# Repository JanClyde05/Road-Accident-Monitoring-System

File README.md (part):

# Road Accident Monitoring System (RAMS)

**Real-Time Highway Incident Detection, LoRa Long-Range Telemetry, Dual-Tier Edge AI, and Rescuer Command Center**

RAMS is an end-to-end, multi-tier emergency response platform engineered for real-time traffic accident detection and immediate rescue dispatch. Designed specifically for highway environments and rural road segments vulnerable to cellular coverage dropouts, RAMS pairs a custom wearable sensor relay node with high-rate inertial shock sensing, off-grid 433MHz LoRa long-range radio broadcast, dual-tier on-device neural edge classification, rider mobile telemetry synchronization, conversational voice AI, and a standalone command-center desktop application.

---

## 1. System Architecture & Information Pipeline

```
  +-------------------------------------------------------------------------------+
  |                             RIDER TIER (MOBILE)                               |
  |  Android Companion App (Kotlin / Jetpack Compose / Edge AI Engine)            |
  |  - 50Hz Continuous Inertial Sensing (Fused Accel/Gyro + Euler Horizon)        |
  |  - Dual-Tier Edge AI: 1D-CNN Kinematic Feature Extractor + SLM Reasoner       |
  |  - 100% Offline On-Device Voice AI Assistant & Wake-Word Canceler ("Hey RAMS")|
  |  - Background System Overlay: Pop-up AI assistant over Facebook / other apps  |
  |  - Dual-Band GNSS Coordinate Acquisition & Offline Hotspot Hazard Density     |
  |  - Medical & Identity Profile Management (Base62 Token, Photo CDN)            |
  |  - Cellular Fallback: Automated SMS Emergency Dispatch & Cloud REST Relay     |
  +---------------------------------------+---------------------------------------+
                                          |
                              BLE GATT (0xFFE0 / 0xFFE1)
                                          |
                                          v
  +-------------------------------------------------------------------------------+
  |                            WEARABLE RELAY TIER                                |
  |  RAMS Custom Wearable PCB (ESP32-S3FH4R2, Rev C EPDC Edition)                 |
  |  - 2-Stage Finite State Machine (Freefall -> Impact Spike -> Rest -> Latch)   |
  |  - On-Board MPU-6050 Motion Engine & Crash Logic (100Hz I2C)                  |
  |  - 30-Second Auditory / Visual Warning & False-Alarm Cancellation Button      |
  |  - WS2812B RGB Status Indication (Armed, SOS Alert, Low Battery)              |
  |  - On-Board Battery Management (TP4054 Charger + DW01A/FS8205A Protection)   |
  +---------------------------------------+---------------------------------------+
                                          |
                        433MHz LoRa Link (SX1278, SF9, CR 4/5)
                                          |
                                          v
  +-------------------------------------------------------------------------------+
  |                         BASE STATION RECEIVER TIER                            |
  |  LoRa Ground Station (ESP32-S3 Base Unit)                                     |
  |  - Continuous 433MHz Carrier Monitoring (SX1278 SPI Interface)               |
  |  - Dual-Stream Output: High-Speed USB Serial & Local Wi-Fi TCP/HTTP Bridge    |
  |  - LittleFS Offline Flash Store-and-Forward Emergency Queue                   |
  +-------------------+---------------------------------------+-------------------+
                      |                                       |
              USB Serial (115200)                      Wi-Fi / LAN TCP (8888)
                      |                                       |
                      +-------------------+-------------------+
                                          v
  +-------------------------------------------------------------------------------+
  |                        COMMAND CENTER & DISPATCH TIER                         |
  |  Windows Rescuer Desktop Application (C# .NET + React 19 / Leaflet Radar)     |
  |  - Zero-Configuration COM Port Auto-Detection & USB Ingestion Engine          |
  |  - Real-Time Incident Triage, Audible Klaxon Alerts, & Priority Queuing       |
  |  - Interactive Tactical Radar Map with Live Marker Tracking & ETA Calculation |
  |  - Spatial Machine Learning Hotspot Predictor & Incident Heatmap              |
  |  - Local JSON Data Persistence (incidents.json, registrations.json)           |
  |  - Netlify Cloud Backend Integration & Public Web Map Mirror                  |
  +-------------------------------------------------------------------------------+
```

---

## 2. Master Navigation Index: Focus Folders & Core Entry Points

This directory routing table allows human engineers and AI agents to locate and navigate every functional subsystem directly:

| Subsystem Domain | Primary Focus Folder | Key Entry Points & Core Files | Role & Capabilities |
|---|---|---|---|
| **Android Mobile App** | [`apps/android_app/`](file:///d:/Antigravity/Projects/Danger%20Monitoring%20System%20V2/apps/android_app/) | [`MainActivity.kt`](file:///d:/Antigravity/Projects/Danger%20Monitoring%20System%20V2/apps/android_app/app/src/main/java/com/example/MainActivity.kt)<br>[`RamsViewModel.kt`](file:///d:/Antigravity/Projects/Danger%20Monitoring%20System%20V2/apps/android_app/app/src/main/java/com/example/viewmodel/RamsViewModel.kt)<br>[`AndroidManifest.xml`](file:///d:/Antigravity/Projects/Danger%20Monitoring%20System%20V2/apps/android_app/app/src/main/AndroidManifest.xml) | Production Android Kotlin / Jetpack Compose application. Houses BLE GATT, GPS, real-time telemetry, and foreground service. |
| **Edge AI & Assistant** | [`apps/android_app/.../ai/`](file:///d:/Antigravity/Projects/Danger%20Monitoring%20System%20V2/apps/android_app/app/src/main/java/com/example/ai/) | [`SensorAiInferenceEngine.kt`](file:///d:/Antigravity/Projects/Danger%20Monitoring%20System%20V2/apps/android_app/app/src/main/java/com/example/ai/SensorAiInferenceEngine.kt)<br>[`VoiceAlarmCanceler.kt`](file:///d:/Antigravity/Projects/Danger%20Monitoring%20System%20V2/apps/android_app/app/src/main/java/com/example/ai/VoiceAlarmCanceler.kt)<br>[`RamsAiAssistantEngine.kt`](file:///d:/Antigravity/Projects/Danger%20Monitoring%20System%20V2/apps/android_app/app/src/main/java/com/example/ai/RamsAiAssistantEngine.kt) | Dual-tier edge neural model, 100% offline "Hey RAMS" wake-word recognizer, and personalized conversational companion. |
| **Standalone AI Suite** | [`apps/new_ai_applications/`](file:///d:/Antigravity/Projects/Danger%20Monitoring%20System%20V2/apps/new_ai_applications/) | [`mobile_ai_app/`](file:///d:/Antigravity/Projects/Danger%20Monitoring%20System%20V2/apps/new_ai_applications/mobile_ai_app/)<br>[`ai_resources_and_models/`](file:///d:/Antigravity/Projects/Danger%20Monitoring%20System%20V2/apps/new_ai_applications/ai_resources_and_models/)<br>[`FREE_MOTION_DATASETS_DIRECTORY.md`](file:///d:/Antigravity/Projects/Danger%20Monitoring%20System%20V2/apps/new_ai_applications/ai_resources_and_models/FREE_MOTION_DATASETS_DIRECTORY.md) | Synchronized standalone twin applications, motion benchmark datasets, and 1-click build pipelines. |
| **Wearable Firmware** | [`firmware/wearable_withApp/`](file:///d:/Antigravity/Projects/Danger%20Monitoring%20System%20V2/firmware/wearable_withApp/) | [`wearable_withApp.ino`](file:///d:/Antigravity/Projects/Danger%20Monitoring%20System%20V2/firmware/wearable_withApp/wearable_withApp.ino) | ESP32-S3 firmware with MPU-6050 100Hz FSM, ATGM336H GPS parsing, SX1278 LoRa uplink, BLE GATT server, and WS2812B NeoPixel. |
| **Base Station Firmware** | [`firmware/receiver_withDesktop/`](file:///d:/Antigravity/Projects/Danger%20Monitoring%20System%20V2/firmware/receiver_withDesktop/) | [`receiver_withDesktop.ino`](file:///d:/Antigravity/Projects/Danger%20Monitoring%20System%20V2/firmware/receiver_withDesktop/receiver_withDesktop.ino) | ESP32-S3 base station listening on 433MHz LoRa. Forwards alerts over USB Serial (`RAMS_PKT:...`) and Wi-Fi TCP/HTTP. |
| **Shared RF Protocol** | [`firmware/shared/`](file:///d:/Antigravity/Projects/Danger%20Monitoring%20System%20V2/firmware/shared/) | [`protocol.h`](file:///d:/Antigravity/Projects/Danger%20Monitoring%20System%20V2/firmware/shared/protocol.h) | Canonical C header defining packed binary RF structs (`LoRaAlertPacket`, `TelemetryPacket`), bitmasks, and RF channels. |
| **Command Center Desktop** | [`apps/desktop_app/`](file:///d:/Antigravity/Projects/Danger%20Monitoring%20System%20V2/apps/desktop_app/) | [`RescuerForm.cs`](file:///d:/Antigravity/Projects/Danger%20Monitoring%20System%20V2/apps/desktop_app/RescuerForm.cs)<br>[`HotspotPredictor.cs`](file:///d:/Antigravity/Projects/Danger%20Monitoring%20System%20V2/apps/desktop_app/HotspotPredictor.cs)<br>[`www/index.html`](file:///d:/Antigravity/Projects/Danger%20Monitoring%20System%20V2/apps/desktop_app/www/index.html) | Windows Rescuer Operations app (C# .NET / WebView2 + React 19). Handles serial auto-detect, klaxon alerts, and incident triage. |
| **Cloud Web Mirror** | [`apps/backend/`](file:///d:/Antigravity/Projects/Danger%20Monitoring%20System%20V2/apps/backend/) | [`src/App.tsx`](file:///d:/Antigravity/Projects/Danger%20Monitoring%20System%20V2/apps/backend/src/App.tsx)<br>[`netlify.toml`](file:///d:/Antigravity/Projects/Danger%20Monitoring%20System%20V2/apps/backend/netlify.toml) | React 19 / Leaflet live dispatch map hosted on Netlify Serverless for supervisor and field hospital visibility. |
| **Hardware & PCB CAD** | [`hardware/KiCAD Files/Antigravity Build/RAMS - PCB - Rev C/`](file:///d:/Antigravity/Projects/Danger%20Monitoring%20System%20V2/hardware/KiCAD%20Files/Antigravity%20Build/RAMS%20-%20PCB%20-%20Rev%20C/) | [`RAMS - PCB.kicad_sch`](file:///d:/Antigravity/Projects/Danger%20Monitoring%20System%20V2/hardware/KiCAD%20Files/Antigravity%20Build/RAMS%20-%20PCB%20-%20Rev%20C/RAMS%20-%20PCB.kicad_sch)<br>[`RAMS - PCB.kicad_pcb`](file:///d:/Antigravity/Projects/Danger%20Monitoring%20System%20V2/hardware/KiCAD%20Files/Antigravity%20Build/RAMS%20-%20PCB%20-%20Rev%20C/RAMS%20-%20PCB.kicad_pcb)<br>[`circuit_spec.json`](file:///d:/Antigravity/Projects/Danger%20Monitoring%20System%20V2/hardware/KiCAD%20Files/Antigravity%20Build/RAMS%20-%20PCB%20-%20Rev%20C/circuit_spec.json) | Production Rev C EPDC-compliant PCB CAD (DOST-ASTI EPDC manufacturing rules: 0.3mm trace, 0.4mm drill, 0.95mm via). |
| **Data & Research Docs** | [`docs/`](file:///d:/Antigravity/Projects/Danger%20Monitoring%20System%20V2/docs/) | [`FREE_MOTION_DATASETS_DIRECTORY.md`](file:///d:/Antigravity/Projects/Danger%20Monitoring%20System%20V2/docs/FREE_MOTION_DATASETS_DIRECTORY.md)<br>[`00_SYSTEM_ARCHITECTURE.md`](file:///d:/Antigravity/Projects/Danger%20Monitoring%20System%20V2/00_SYSTEM_ARCHITECTURE.md)<br>[`MEMORY_MAP.md`](file:///d:/Antigravity/Projects/Danger%20Monitoring%20System%20V2/MEMORY_MAP.md) | Architectural documentation, dataset directories, validation matrices, and DOST procurement specifications. |

---

## 3. Scientific References, Standards & Open Datasets Used

The design, mathematical formulations, sensor calibration, and physical validation of RAMS are built upon peer-reviewed research, international engineering standards, and public benchmark datasets:

### 3.1 Open-Source Motion Datasets & Kinematic Benchmarks
* **SisFall Dataset** (*Universidad de Antioquia, Colombia*):
  - 4,510 recorded trials across 38 subjects using dual 3-axis accelerometers (ADXL345, MMA8451Q) and ITG3200 gyroscope at 200 Hz.
  - Used to calibrate human fall kinematics, pre-impact freefall boundaries, and post-fall rest posture.
  - Source: [Zenodo 57233](https://zenodo.org/record/57233).
* **MobiFall & MobiAct Dataset** (*Biomedical Informatics & eHealth Laboratory, HMU Greece*):
  - 3,200 trials across 67 participants recording pocket smartphone IMU vectors at 87 Hz.
  - Used to benchmark trouser-pocket smartphone movement during walking, running, stumbling, and vehicle transit.
  - Source: [MobiAct HMU](https://www.bmi.hmu.gr/the-mobiact-dataset/).
* **UP-Fall Detection Dataset** (*Universidad Panamericana, Mexico*):
  - Multi-IMU dataset (waist, wrist, neck, thigh, ankle) at 100 Hz.
  - Used to correlate wrist wearable kinematics against waist/pocket smartphone telemetry.
  - Source: [Zenodo 3739768](https://zenodo.org/record/3739768).
* **IEEE DataPort Road Pothole & Speed Bump Dataset** (*IEEE DataPort*):
  - 50 Hz tri-axial accelerometer & gyroscope recordings from motorcycles and passenger vehicles over road anomalies.
  - Used for **False-Positive Suppression**: establishing the vertical shockwave recovery signature ($>4.0G$ vertical impulse returning to $0^\circ$ upright within 300 ms).
  - Source: [IEEE DataPort Pothole Dataset](https://ieee-dataport.org/open-access/road-pothole-and-bump-dataset).
* **UCI Human Activity Recognition (HAR) Smartphone Dataset** (*UCI ML Repository*):
  - 10,299 instances of 50 Hz waist-mounted smartphone data across walking, stair climbing, sitting, and standing.
  - Used as the nominal Activities of Daily Living (ADL) control group to ensure zero false triggers during pedestrian transit.
  - Source: [UCI HAR Repository](https://archive.ics.uci.edu/dataset/240/human+activity+recognition+using+smartphones).

### 3.2 Hardware Standards & Semiconductor Specifications
* **InvenSense MPU-6050 Motion Processing Unit**:
  - $I^2C$ fast-mode protocol, internal digital low-pass filtering (DLPF 44Hz), $\pm 16g$ accelerometer full-scale, $\pm 2000^\circ/s$ gyroscope range.
* **Semtech SX1278 LoRa Transceiver**:
  - 433MHz ISM physical layer, Spreading Factor 9, 125 kHz Bandwidth, Coding Rate 4/5, $+17\text{ dBm}$ output power, link budget $>148\text{ dB}$.
* **Espressif ESP32-S3FH4R2 Microcontroller**:
  - Dual-core Xtensa LX7 @ 240MHz with vector instructions, 4MB embedded Flash, 2MB embedded PSRAM, Bluetooth 5.0 LE GATT peripheral.
* **DOST-ASTI EPDC PCB Design Rules**:
  - Electronics Product Development Center, Department of Science and Technology, Bicutan, Taguig.
  - Minimum track width: $0.30\text{ mm}$, track clearance: $0.254\text{ mm}$, mechanical drill: $0.40\text{ mm}$, via diameter: $0.95\text{ mm}$.

---

## 4. Production Methodologies & Technical Engineering

### 4.1 Kinematic Feature Extraction Pipeline (14 Canonical Parameters)
RAMS samples the phone's 6-axis IMU (fused accelerometer and calibrated gyroscope) at 50 Hz through a 50-sample sliding window ($1000\text{ ms}$ duration with $200\text{ ms}$ overlap). For each window, the kinematic pipeline computes a 14-parameter feature vector:

$$\text{SVM}_i = \sqrt{a_{x,i}^2 + a_{y,i}^2 + a_{z,i}^2}$$

1. **Mean SVM ($G$)**: Baseline gravitational loading and continuous propulsion.
2. **Peak Shock SVM ($G$)**: Maximum impact impulse ($>4.5G$ for severe collisions; $2.5G\text{--}4.0G$ for road bumps).
3. **Minimum Freefall SVM ($G$)**: Airborne / drop detection ($<0.35G$ signals weightlessness).
4. **SVM Standard Deviation ($G$)**: Roughness and kinematic variance dispersion.
5. **Root Mean Square SVM ($G$)**: Continuous kinetic energy density.
6. **Peak Gyroscope Magnitude ($^\circ/s$)**: Maximum angular tumbling velocity.
7. **Mean Gyroscope Magnitude ($^\circ/s$)**: Sustained angular rotation.
8. **Gyroscope Standard Deviation ($^\circ/s$)**: Rotational stability index.
9. **Maximum Jerk ($G/s$)**: $\max(\|\text{SVM}_i - \text{SVM}_{i-1}\| \times 50)$, measuring shockwave sharpness.
10. **Mean Jerk ($G/s$)**: Continuous rate of acceleration change.
11. **Tilt Delta ($^\circ$)**: $\|\Delta\text{Pitch}\| + \|\Delta\text{Roll}\|$. **The critical discriminator**: genuine crashes rest at $>45^\circ$, while potholes and speed bumps immediately recover to upright ($<5^\circ$).
12. **Signal Magnitude Area (SMA)**: Activity energy normalized over the window.
13. **Spectral Energy (SVM)**: Energy dissipation across the shock window.
14. **Zero-Crossing Rate**: Cyclic cadence used to detect walking ($1.5\text{--}2.0\text{ Hz}$) and running ($2.5\text{--}3.5\text{ Hz}$) while suppressing false alarms.

### 4.2 False Alarm Rejection & Hysteresis Logic
Naive impact detectors trigger 911 alarms whenever a phone is dropped or hits a bump. RAMS enforces strict **zero false-alarm suppression rules**:
* **Potholes & Speed Bumps**: Vertical spike up to $4.5G$ with $\text{Tilt Delta} < 10^\circ$ and immediate recovery $\rightarrow$ `SUPPRESSED: ROAD POTHOLE` (0% Risk).
* **Stationary Phone Drops**: Drop shock up to $3.5G$ at $0\text{ km/h}$ pre-event speed $\rightarrow$ `SUPPRESSED: STATIONARY DROP` (0% Risk).
* **Pocket Tremors & Hand Shakes**: High-frequency gyro tremor without vehicular speed $\rightarrow$ `SUPPRESSED: POCKET VIBRATION` (0% Risk).
* **Pedestrian Gait**: Cyclic zero-crossing rate ($1.2\text{--}3.0\text{ Hz}$) with $1.0G$ baseline $\rightarrow$ `SUPPRESSED: PEDESTRIAN ADL` (0% Risk).
* **Temporal Hysteresis**: Transitions require 3 consecutive matching windows, preventing AI decision flutter, while true accidents trigger immediately ($0\text{ ms}$ latency).

### 4.3 100% Offline Conversational Voice AI & Background Overlay
* **Continuous Microphone Listener**: Android On-Device Speech Recognition (`createOnDeviceSpeechRecognizer`) backed by Android System Intelligence (`com.google.android.as`), operating 100% offline without network connections.
* **Phonetic Normalization**: Strips punctuation and matches phonetic variants (`"Hey RAMS"`, `"Hi RAMS"`, `"Hey Ram"`, `"OK RAMS"`, `"RAMS"`).
* **Background System Overlay (`SYSTEM_ALERT_WINDOW`)**: When the rider says "Hey RAMS" while using Facebook, Google Maps, or browsing the home screen, the app immediately summons the translucent Assistant Bubble over the current screen.
* **Adaptive Conversational Persona**: Personalizes every response to the registered user type (Motorcycle Rider vs Pedestrian vs Car Driver vs Cyclist) using live telemetry, weather, medical tokens, and comprehensive app technical guidance.

---

## 5. Build, Setup & Quick Start Guide

### Prerequisites
* **Android Studio Ladybug (or newer)** with Android SDK 34+.
* **Arduino IDE 2.x** with the ESP32 Board Support Package (by Espressif Systems).
* **Windows 10 / 11** with .NET Framework 4.8+.
* **Node.js 20+** and `npm` (for backend/desktop web builds).
* **KiCad 10** (for schematic review and PCB generation).

### 1-Click Batch Scripts (in `apps/`)
* [`apps/Build_Android_APK.bat`](file:///d:/Antigravity/Projects/Danger%20Monitoring%20System%20V2/apps/Build_Android_APK.bat) — Compiles and packages the native Android APK (`app-debug.apk`).
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
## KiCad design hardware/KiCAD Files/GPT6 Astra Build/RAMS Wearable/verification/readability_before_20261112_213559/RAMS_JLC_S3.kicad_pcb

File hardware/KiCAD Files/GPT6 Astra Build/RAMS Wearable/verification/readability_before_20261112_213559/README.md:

# RAMS wearable — JLCPCB J2 engineering candidate

**2026-11-09 owner correction: simplify around the working S3 Supermini prototype.**

The current native schematic and board are **J2, a 3.3 V AP2112 LDO design**, with a separate switched raw battery/USB supply for the RGB LED. The earlier TPS63020 buck-boost / 3.45 V candidate is superseded and archived. **Routing is complete: KiCad 10.0.6 reports zero ERC/DRC violations, zero unconnected items and zero schematic mismatches on 2026-11-12.** Read [final validation](reports/FINAL_VALIDATION.md) for source hashes and limits. **This is an engineering candidate, not a manufacturing release or physically proven board.**

The owner wants the functions of the working ESP32-S3 Supermini, Ra-02, active buzzer, battery divider and single 3.7 V LiPo integrated onto one customized bare-chip PCB. The buzzer clarification is resolved: a DC supply produces a tone, and the owned stock is `9650 Active 3V`. Minimize cost and additional purchases. Preserve the original 42 x 32 mm envelope, top-side heatbed assembly and bottom-side hand-soldered LoRa. The unknown-reflow-rated buzzer is hand-soldered after reflow using accessible lands. DOST remains deferred.

See [the corrected design brief](docs/SIMPLIFICATION_20261109.md). The superseded native sources and generator are retained with hashes in `verification/superseded_buckboost_20261109/`. Original Antigravity Rev A/B/C files remain untouched.

J2 uses owned AP2112K-3.3, LTC4054/LTH7 charger, protection and NPN buzzer driver. The ADC uses one DMN2056U-7 MOSFET with a 30k/10k divider: build with `RAMS_JLC_S3_J2` for calibrated millivolt reads and ratio 4; the default SuperMini configuration retains ratio 2. Reset uses a conventional 10k/1uF RC. See [parts and firmware](docs/PARTS_AND_FIRMWARE.md).

The ordered WS2812B-2020 listing says DC5V and does not identify its exact revision. **Q5, another owned AO3401, switches raw SYS_IN power to LED_PWR** for battery and USB operation. SW1 grounds Q5's gate in ON and LDO enable in OFF; R7 and R41 are pull-ups, so the switch carries only control current. **U6 SN74LVC1T45DBVR translates GPIO48 data to the LED supply and provides power-off isolation**. C34 and C35 independently bypass its two supplies; C28 bypasses LED1. This is a logic translator, not a power converter. See [raw LED supply review](docs/LED_RAW_SUPPLY_REVIEW.md).

LED1 is left unpopulated for initial power checks, then fitted for normal RGB operation after stock geometry, polarity, minimum voltage and current are qualified. Its reference pinout is 1 DO unused, 2 GND, 3 DI, 4 LED_PWR. A nominal 3.7 V cell does not stay at 3.7 V: determine the final low-battery threshold from the accepted LED range as well as the MCU rail. No guarantee of full-discharge LED operation is made.

The [BOM](docs/BOM_PROCUREMENT.csv) contains **90 footprint positions: 82 components and 8 copper test pads**. First power-on uses 80 components, leaving R30 and LED1 absent; normal use fits both after their separate checks. Reuse the owned AP2112, buzzer, switches and suitable passives. Follow [assembly and bring-up](docs/ASSEMBLY_AND_BRINGUP.md) for top heatbed reflow, then buzzer and bottom Ra-02 hand soldering.

Open the native [KiCad project](RAMS_JLC_S3.kicad_pro) or [PCB](RAMS_JLC_S3.kicad_pcb). The [review package](manufacturing/ENGINEERING_REVIEW_20261112/READ_ME_FIRST.md) contains frozen sources, fabrication artwork, drill files, schematic/assembly PDFs and separate first-power/normal top stencils. Nothing was uploaded or ordered. See [JLC manufacturing review](docs/JLC_MANUFACTURING_REVIEW.md) for the remaining impedance, stock-fit and soldering-process gates. Physical charging, thermal, USB, LED, ADC and RF validation follows assembly.

The **native PCB is authoritative**. Initial placement and critical-route JSON files are historical construction inputs; they do not reproduce the final routed board. Construction scripts now refuse destructive regeneration of the active design. Read [script workflow](scripts/README.md) before running any generator. The footprint includes 0.25 mm ESP32 perimeter lands and 0.20 mm-wide paste openings for JLC DFM; nine exposed-pad thermal vias and their soldering process still require qualification.

No fabricated boards or physical measurements exist for this project. R30 enables nominal 100 mA charging after the selected 500/1000 mAh cell and harness checks; capacity alone does not establish the permitted charge current. The preserved firmware percentage endpoint is now 3.55 V; it is a display calibration, not automatic shutdown or proof of the regulator/LED operating floor. Both current J2 and Supermini builds and host tests pass.

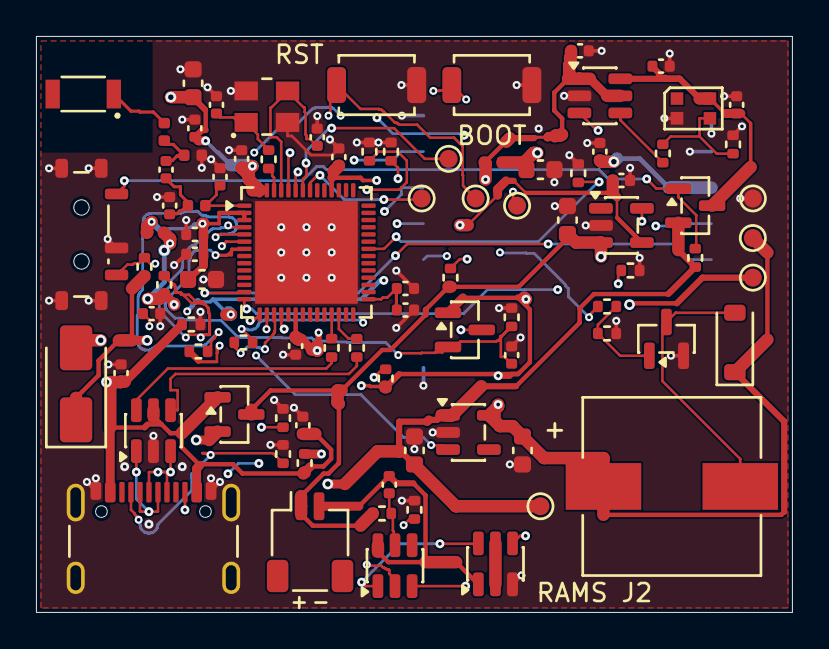
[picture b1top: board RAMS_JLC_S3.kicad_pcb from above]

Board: 4 copper layers, 42.0 x 32.0 mm, 90 parts (1 on the bottom side), 55 nets.

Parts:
ANT1: 2450AT18B100E; Johanson_B100_3216
BZ1: 9650 Active 3V STOCK; Buzzer_9650_SMD_Stock_HandSolder
C1, C3: 1uF 10V X7R; C_0402_1005Metric
C2, C5, C13, C15, C16, C20, C27, C28, C34, C35: 100nF X7R; C_0402_1005Metric
C4: 4.7uF 10V X5R; C_0603_1608Metric
C7, C10: 10uF 16V X5R; C_0603_1608Metric
C11, C14, C26: 10uF 10V X5R; C_0603_1608Metric
C12, C17, C22, C33: 1uF X7R; C_0402_1005Metric
C18, C19: 1.5pF C0G RF; C_0402_1005Metric
C21: 10nF X7R; C_0402_1005Metric
C24, C25: 12pF C0G; C_0402_1005Metric
C29: 1nF X7R; C_0402_1005Metric
C32: 1.2pF C0G RF; C_0402_1005Metric
D1: USBLC6-2SC6; SOT-23-6
D2: SS14 SMA; D_SMA
D3: 1N4148W; D_SOD-123
FB1: MGGB1005M800HT-LF; L_0402_1005Metric
J1: USB4105-GF-A; USB_C_Receptacle_GCT4105_NPTH
J2: SM02B-SRSS-TB; JST_SH_SM02B-SRSS-TB_1x02-1MP_P1.00mm_Horizontal
L1: 2.0nH >=500mA; L_0402_1005Metric
L2: 2.4nH RF; L_0402_1005Metric
L4: 2.7nH RF; L_0402_1005Metric
L5: 3.3nH RF; L_0402_1005Metric
LED1: WS2812B-2020 STOCK VERIFY; LED_WS2812B-2020_PLCC4_2.0x2.0mm
Q1, Q5: AO3401A; SOT-23
Q2: BC817-25; SOT-23
Q3: FS8205A Fuxin; SOT-23-6
Q4: DMN2056U-7; SOT-23
R1, R2: 5.1k 1%; R_0402_1005Metric
R3, R16: 10k 1%; R_0402_1005Metric
R4: 100R; R_0402_1005Metric
R5: 1k; R_0402_1005Metric
R6, R7, R14, R41, R42, R43: 100k; R_0402_1005Metric
R8, R34, R35, R36, R37: 10k; R_0402_1005Metric
R9, R38, R39: 22R; R_0402_1005Metric
R11, R13: 33R; R_0402_1005Metric
R12: 330R; R_0402_1005Metric
R15: 30k 1%; R_0402_1005Metric
R30: 0R CHG_LINK; R_0402_1005Metric
SW1: MSK12C02; SW_SPDT_Shouhan_MSK12C02
SW2: 3x4mm RESET; SW_SPST_TS-1088-xR020
SW3: 3x4mm BOOT/CANCEL; SW_SPST_TS-1088-xR020
TP1: GND; TestPoint_Pad_D1.0mm
TP2: +3V3; TestPoint_Pad_D1.0mm
TP3: B_PLUS; TestPoint_Pad_D1.0mm
TP4: UART_TX; TestPoint_Pad_D1.0mm
TP5: UART_RX; TestPoint_Pad_D1.0mm
TP6: MCU_EN; TestPoint_Pad_D1.0mm
TP7: BOOT_BTN; TestPoint_Pad_D1.0mm
TP8: SYS_IN; TestPoint_Pad_D1.0mm
U1: ESP32-S3FH4R2; ESP32-S3FH4R2_QFN56_EP5p7
U2: Ai-Thinker-Ra-02; Ai-Thinker-Ra-01-LoRa
U3: LTC4054ES5-4.2; TSOT-23-5
U4: DW01A SLKOR; SOT-23-6
U5: AP2112K-3.3TRG1; SOT-23-5
U6: SN74LVC1T45DBVR; SOT-23-6
Y1: ABM8-40.000MHZ-10-1-U-T; Crystal_Abracon_ABM8_3225

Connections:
+3V3: BZ1.1, C10.1, C14.1, C15.1, C16.1, C21.1, C22.1, C34.1, D3.1, FB1.1, L1.1, Q4.1, R8.1, R34.1, R37.1, TP2.1, U1.20, U1.46, U1.55, U1.56, U5.5, U6.1, U6.5
ANT_FEED: ANT1.1, L5.2
ANT_TUNE: C32.2, L4.1, L5.1
BOOT_BTN: R34.2, SW3.1, TP7.1, U1.5
BUZZER_BASE: Q2.1, R12.2, R14.1
BUZZER_CTRL: R12.1, U1.6
BUZZER_NEG: BZ1.2, D3.2, Q2.3
B_MINUS: C5.2, J2.2, Q3.1, U4.6
B_PLUS: C4.1, J2.1, Q1.3, R4.1, R15.1, TP3.1, U3.3
CC1: J1.A5, R1.1
CC2: J1.B5, R2.1
CHG_IN: C3.1, R30.2, U3.4
CHG_PROG: R3.1, U3.5
DW_CS: R5.1, U4.2
DW_OC: Q3.4, U4.3
DW_OD: Q3.6, U4.1
DW_VCC: C5.1, R4.2, U4.5
FET_DRAIN: Q3.2, Q3.5
GND: C1.2, C2.2, C3.2, C4.2, C7.2, C10.2, C11.2, C12.2, C13.2, C14.2, C15.2, C16.2, C17.2, C18.2, C19.2, C20.2, C21.2, C22.2, C24.2, C25.2, C26.2, C27.2, C28.2, C29.2, C33.2, C34.2, C35.2, D1.2, J1.A1, J1.A12, J1.B1, J1.B12, J1.SH, L4.2, LED1.2, Q2.2, Q3.3, R1.2, R2.2, R3.2, R5.2, R6.2, R14.2, R16.2, R35.2, R36.2, R42.2, R43.2, SW1.2, SW1.SH, SW2.2, SW3.2, TP1.1, U1.57, U2.1, U2.2, U2.9, U2.16, U3.2, U5.2, U6.2, Y1.2, Y1.4
LED_GATE: Q5.1, R41.2, SW1.1
LED_PWR: C28.1, C35.1, LED1.4, Q5.3, U6.6
LORA_DIO0: U1.13, U2.5
LORA_MISO: U1.18, U2.13
LORA_MOSI: U1.16, U2.14
LORA_NSS: R37.2, U1.15, U2.15
LORA_RST: U1.14, U2.4
LORA_SCK: R11.1, U1.17
LORA_SCK_DEV: R11.2, U2.12
LORA_VDD: C26.1, C27.1, FB1.2, U2.3
MCU_EN: C33.1, R8.2, SW2.1, TP6.1, U1.4
NEO_DATA: R42.1, U1.36, U6.3
NEO_DIN: LED1.3, R13.2, R43.1
NEO_SHIFT: R13.1, U6.4
RF_LNA: C18.1, L2.1, U1.1
RF_MATCH: C19.1, C32.1, L2.2
STRAP45: R35.1, U1.51
STRAP46: R36.1, U1.52
SYS_EN: R7.2, SW1.3, U5.3
SYS_IN: C7.1, D2.1, Q1.2, Q5.2, R7.1, R41.1, TP8.1, U5.1
UART_RX: TP5.1, U1.50
UART_TX: TP4.1, U1.49
USB_DN: R39.2, U1.25
USB_DN_CONN: D1.1, J1.A7, J1.B7
USB_DN_ESD: D1.6, R39.1
USB_DP: R38.2, U1.26
USB_DP_CONN: D1.3, J1.A6, J1.B6
USB_DP_ESD: D1.4, R38.1
VBAT_DIV: Q4.3, R15.2
VBAT_SENSE: C29.1, Q4.2, R16.1, U1.7
VBUS: C1.1, C2.1, D1.5, D2.2, J1.A4, J1.A9, J1.B4, J1.B9, Q1.1, R6.1, R30.1
VDD_RF: C11.1, C12.1, C13.1, L1.2, U1.2, U1.3
VDD_SPI: C17.1, C20.1, U1.29
XTAL_N: C25.1, U1.53, Y1.3
XTAL_P: C24.1, R9.2, Y1.1
XTAL_P_DRV: R9.1, U1.54

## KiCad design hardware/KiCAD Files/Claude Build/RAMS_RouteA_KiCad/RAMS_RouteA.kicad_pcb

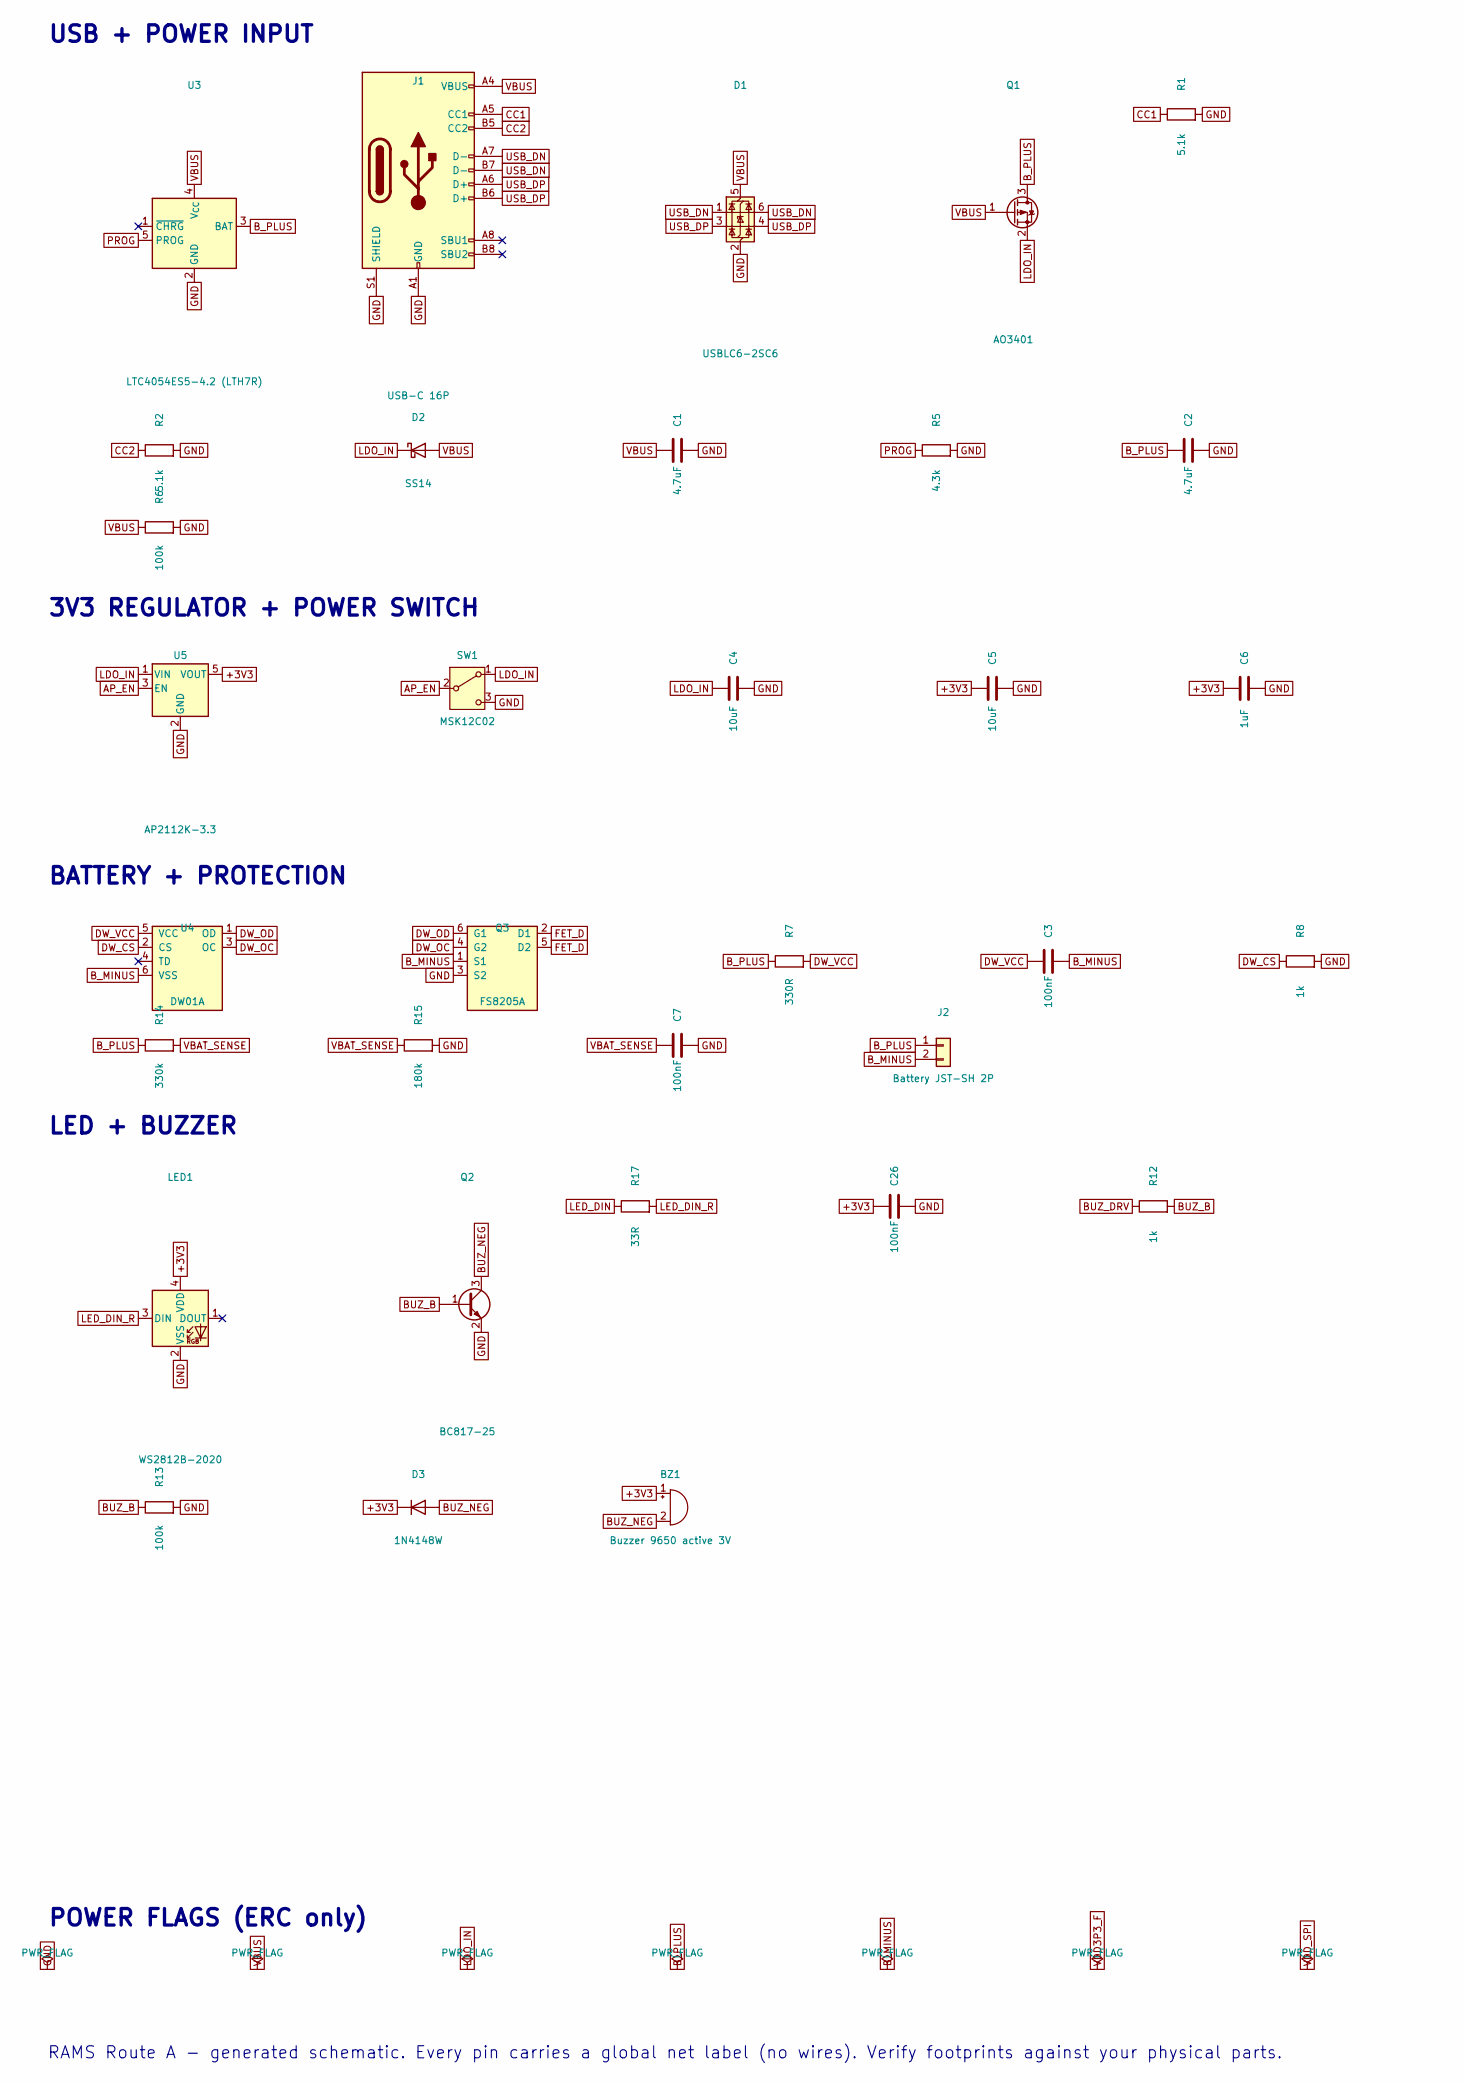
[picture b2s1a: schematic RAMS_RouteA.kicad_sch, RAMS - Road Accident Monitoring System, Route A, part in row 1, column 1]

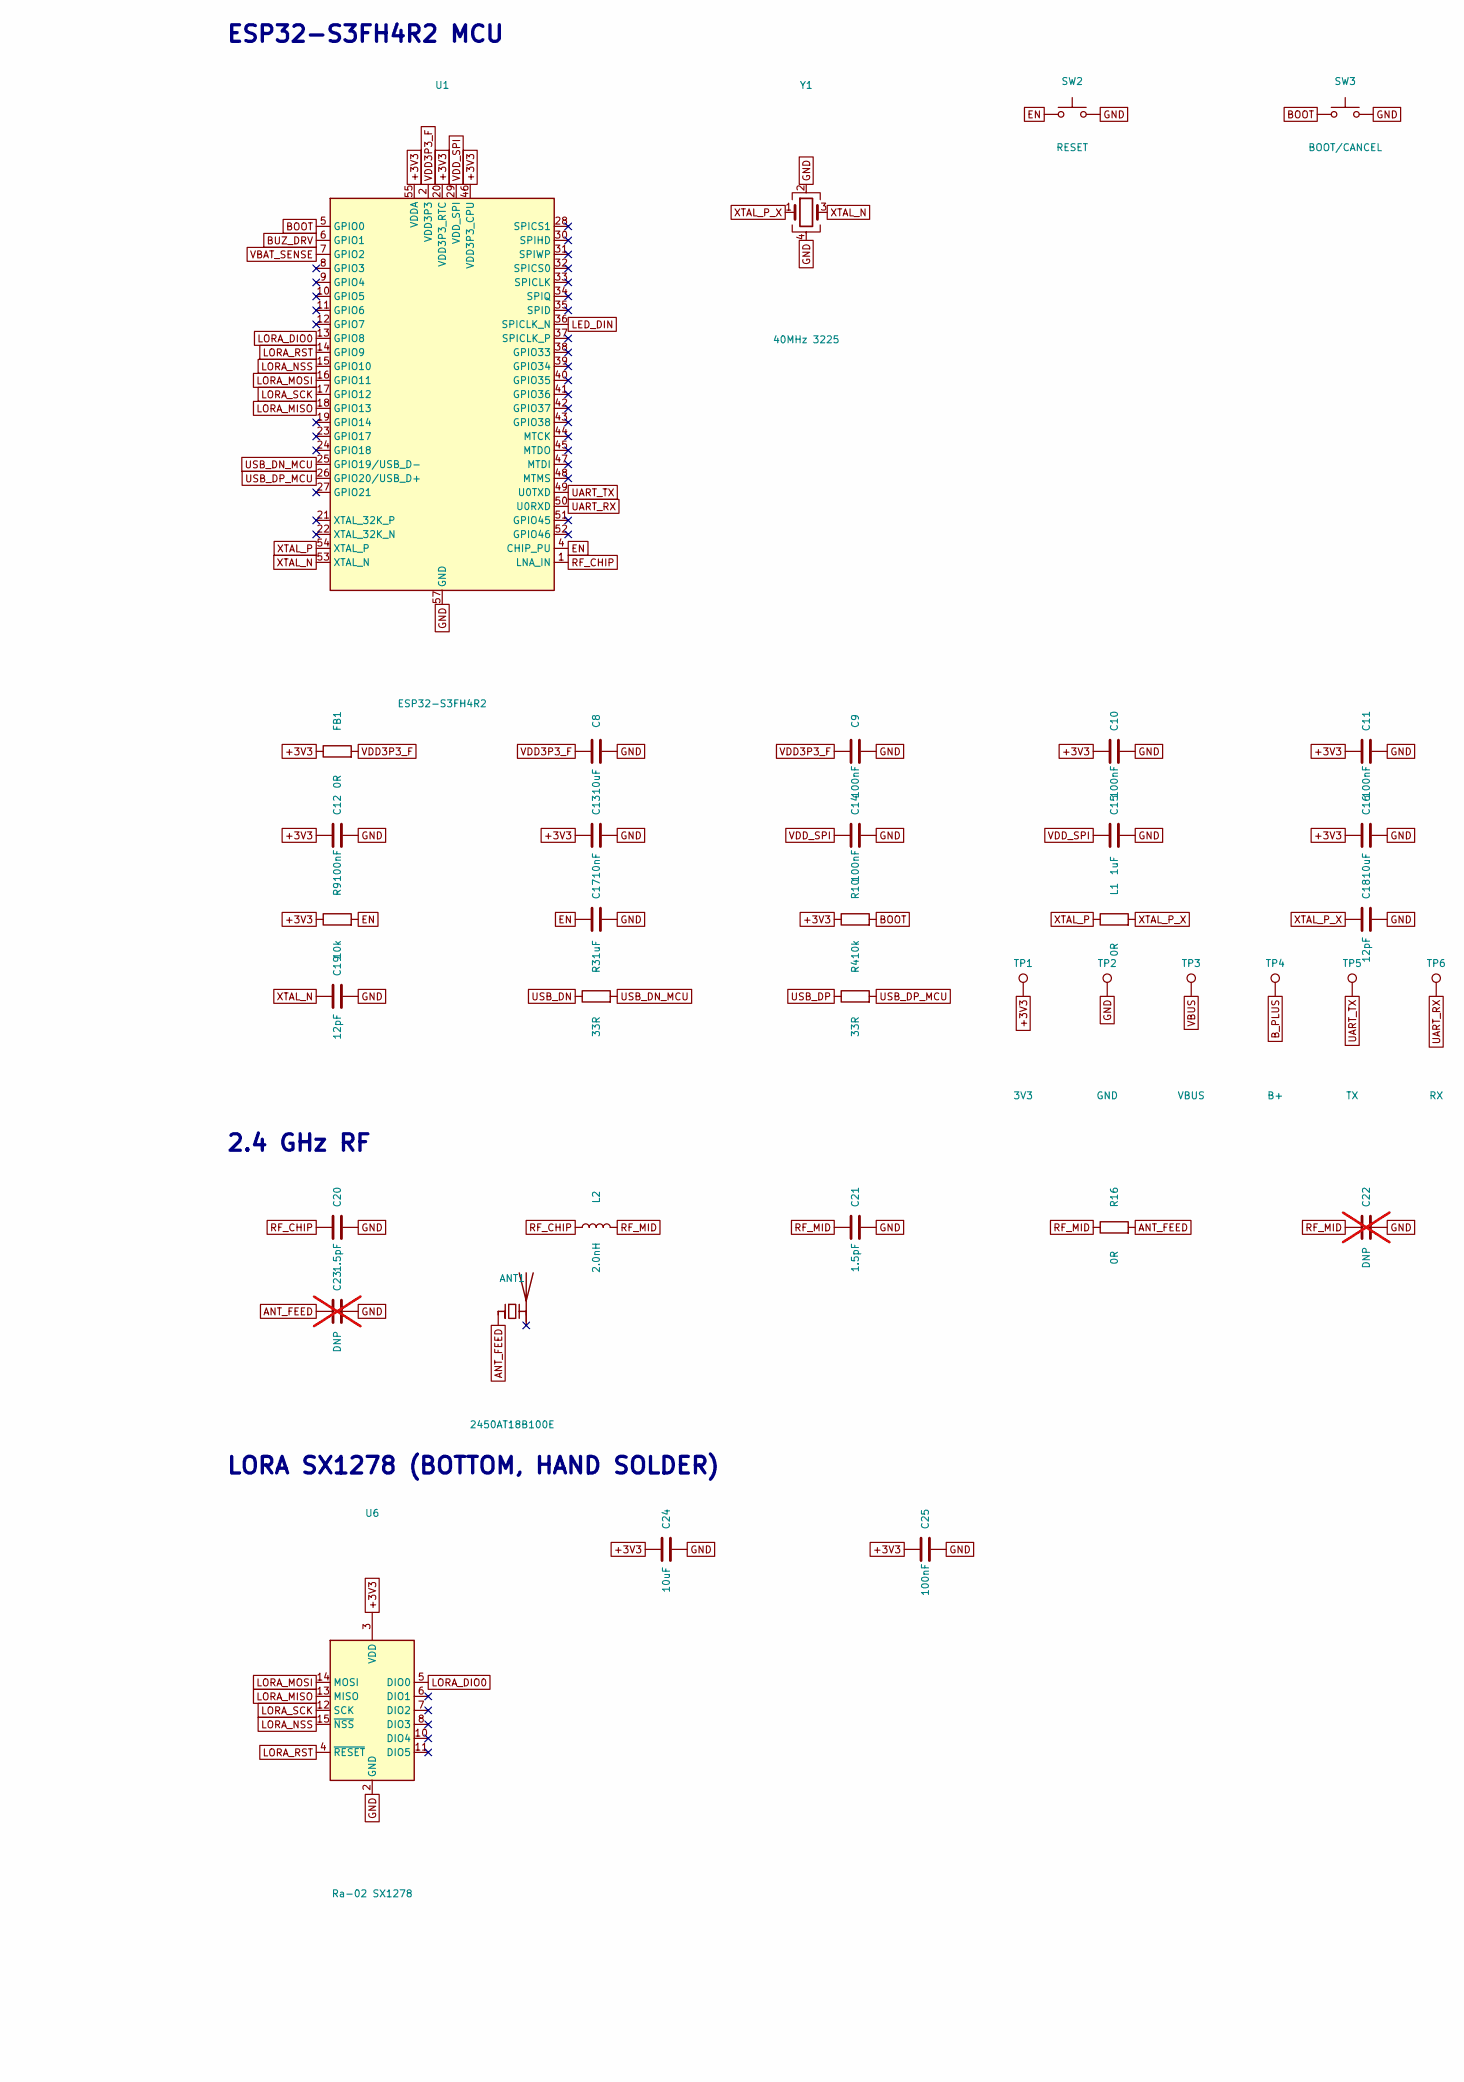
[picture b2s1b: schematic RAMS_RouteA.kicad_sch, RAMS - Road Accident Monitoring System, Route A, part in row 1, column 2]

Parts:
ANT1: 2450AT18B100E; Johanson_2450AT18B100_3216
BZ1: Buzzer 9650 active 3V; Buzzer_SMD_9650
C1, C2: 4.7uF; C_0603_1608Metric
C3, C7, C9, C10, C11, C12, C14, C25, C26: 100nF; C_0402_1005Metric
C4, C5, C8, C16, C24: 10uF; C_0603_1608Metric
C6, C15, C17: 1uF; C_0402_1005Metric
C13: 10nF; C_0402_1005Metric
C18, C19: 12pF; C_0402_1005Metric
C20, C21: 1.5pF; C_0402_1005Metric
C22, C23: DNP; C_0402_1005Metric; not fitted
D1: USBLC6-2SC6; SOT-23-6
D2: SS14; D_SMA
D3: 1N4148W; D_SOD-123
FB1: 0R; R_0402_1005Metric
J1: USB-C 16P; USB_C_Receptacle_HRO_TYPE-C-31-M-12
J2: Battery JST-SH 2P; JST_SH_SM02B-SRSS-TB_1x02-1MP_P1.00mm_Horizontal
L1: 0R; R_0402_1005Metric
L2: 2.0nH; L_0402_1005Metric
LED1: WS2812B-2020; LED_WS2812B-2020_PLCC4_2.0x2.0mm
Q1: AO3401; SOT-23
Q2: BC817-25; SOT-23
Q3: FS8205A; SOT-23-6
R1, R2: 5.1k; R_0805_2012Metric
R3, R4, R17: 33R; R_0402_1005Metric
R5: 4.3k; R_0402_1005Metric
R6, R13: 100k; R_0805_2012Metric
R7: 330R; R_0805_2012Metric
R8, R12: 1k; R_0805_2012Metric
R9, R10: 10k; R_0805_2012Metric
R14: 330k; R_0402_1005Metric
R15: 180k; R_0402_1005Metric
R16: 0R; R_0402_1005Metric
SW1: MSK12C02; SW_SPDT_PCM12
SW2: RESET; SW_Push_1P1T_NO_CK_KMR2
SW3: BOOT/CANCEL; SW_Push_1P1T_NO_CK_KMR2
TP1: 3V3; TestPoint_Pad_D1.5mm
TP2: GND; TestPoint_Pad_D1.5mm
TP3: VBUS; TestPoint_Pad_D1.5mm
TP4: B+; TestPoint_Pad_D1.5mm
TP5: TX; TestPoint_Pad_D1.5mm
TP6: RX; TestPoint_Pad_D1.5mm
U1: ESP32-S3FH4R2; QFN-56-1EP_7x7mm_P0.4mm_EP4x4mm
U3: LTC4054ES5-4.2 (LTH7R); SOT-23-5
U4: DW01A; SOT-23-6
U5: AP2112K-3.3; SOT-23-5
U6: Ra-02 SX1278; Ai-Thinker-Ra-01-LoRa
Y1: 40MHz 3225; Crystal_SMD_3225-4Pin_3.2x2.5mm

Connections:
+3V3: BZ1.1 (+), C5.1, C6.1, C10.1, C11.1, C12.1, C13.1, C16.1, C24.1, C25.1, C26.1, D3.1 (K), FB1.1, LED1.4 (VDD), R9.1, R10.1, TP1.1, U1.20 (VDD3P3_RTC), U1.46 (VDD3P3_CPU), U1.55 (VDDA), U1.56 (VDDA), U5.5 (VOUT), U6.3 (VDD)
ANT_FEED: ANT1.1 (FEED), C23.1, R16.2
AP_EN: SW1.2 (B), U5.3 (EN)
BOOT: R10.2, SW3.1, U1.5 (GPIO0)
BUZ_B: Q2.1 (B), R12.2, R13.1
BUZ_DRV: R12.1, U1.6 (GPIO1)
BUZ_NEG: BZ1.2 (-), D3.2 (A), Q2.3 (C)
B_MINUS: C3.2, J2.2, Q3.1 (S1), U4.6 (VSS)
B_PLUS: C2.1, J2.1, Q1.3 (D), R7.1, R14.1, TP4.1, U3.3 (BAT)
CC1: J1.A5 (CC1), R1.1
CC2: J1.B5 (CC2), R2.1
DW_CS: R8.1, U4.2 (CS)
DW_OC: Q3.4 (G2), U4.3 (OC)
DW_OD: Q3.6 (G1), U4.1 (OD)
DW_VCC: C3.1, R7.2, U4.5 (VCC)
EN: C17.1, R9.2, SW2.1, U1.4 (CHIP_PU)
FET_D: Q3.2 (D1), Q3.5 (D2)
GND: C1.2, C2.2, C4.2, C5.2, C6.2, C7.2, C8.2, C9.2, C10.2, C11.2, C12.2, C13.2, C14.2, C15.2, C16.2, C17.2, C18.2, C19.2, C20.2, C21.2, C22.2, C23.2, C24.2, C25.2, C26.2, D1.2 (GND), J1.A1 (GND), J1.A12 (GND), J1.B1 (GND), J1.B12 (GND), J1.S1 (SHIELD), LED1.2 (VSS), Q2.2 (E), Q3.3 (S2), R1.2, R2.2, R5.2, R6.2, R8.2, R13.2, R15.2, SW1.3 (C), SW2.2, SW3.2, TP2.1, U1.57 (GND), U3.2 (GND), U5.2 (GND), U6.1 (GND), U6.2 (GND), U6.9 (GND), U6.16 (GND), Y1.2, Y1.4
LDO_IN: C4.1, D2.1 (K), Q1.2 (S), SW1.1 (A), U5.1 (VIN)
LED_DIN: R17.1, U1.36 (SPICLK_N)
LED_DIN_R: LED1.3 (DIN), R17.2
LORA_DIO0: U1.13 (GPIO8), U6.5 (DIO0)
LORA_MISO: U1.18 (GPIO13), U6.13 (MISO)
LORA_MOSI: U1.16 (GPIO11), U6.14 (MOSI)
LORA_NSS: U1.15 (GPIO10), U6.15 (~NSS)
LORA_RST: U1.14 (GPIO9), U6.4 (~RESET)
LORA_SCK: U1.17 (GPIO12), U6.12 (SCK)
PROG: R5.1, U3.5 (PROG)
RF_CHIP: C20.1, L2.1, U1.1 (LNA_IN)
RF_MID: C21.1, C22.1, L2.2, R16.1
UART_RX: TP6.1, U1.50 (U0RXD)
UART_TX: TP5.1, U1.49 (U0TXD)
USB_DN: D1.1 (I/O1), D1.6 (I/O1), J1.A7 (D-), J1.B7 (D-), R3.1
USB_DN_MCU: R3.2, U1.25 (GPIO19/USB_D-)
USB_DP: D1.3 (I/O2), D1.4 (I/O2), J1.A6 (D+), J1.B6 (D+), R4.1
USB_DP_MCU: R4.2, U1.26 (GPIO20/USB_D+)
VBAT_SENSE: C7.1, R14.2, R15.1, U1.7 (GPIO2)
VBUS: C1.1, D1.5 (VBUS), D2.2 (A), J1.A4 (VBUS), J1.A9 (VBUS), J1.B4 (VBUS), J1.B9 (VBUS), Q1.1 (G), R6.1, TP3.1, U3.4 (V_{CC})
VDD3P3_F: C8.1, C9.1, FB1.2, U1.2 (VDD3P3), U1.3 (VDD3P3)
VDD_SPI: C14.1, C15.1, U1.29 (VDD_SPI)
XTAL_N: C19.1, U1.53 (XTAL_N), Y1.3
XTAL_P: L1.1, U1.54 (XTAL_P)
XTAL_P_X: C18.1, L1.2, Y1.1

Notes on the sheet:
2.4 GHz RF
ESP32-S3FH4R2 MCU
POWER FLAGS (ERC only)
USB + POWER INPUT
LORA SX1278 (BOTTOM, HAND SOLDER)
BATTERY + PROTECTION
3V3 REGULATOR + POWER SWITCH
RAMS Route A - generated schematic. Every pin carries a global net label (no wires). Verify footprints against your physical parts.
LED + BUZZER

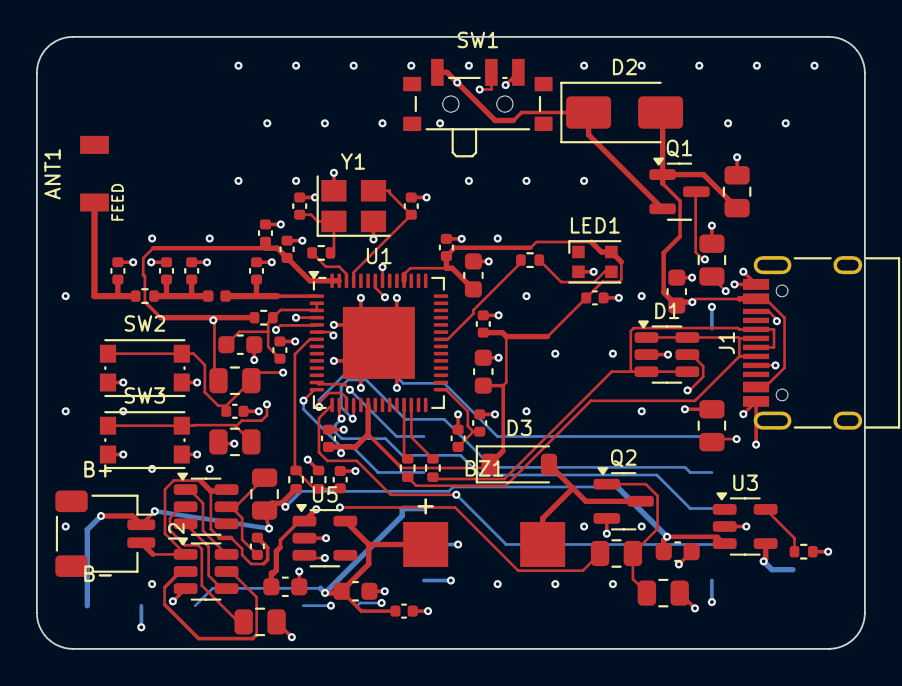
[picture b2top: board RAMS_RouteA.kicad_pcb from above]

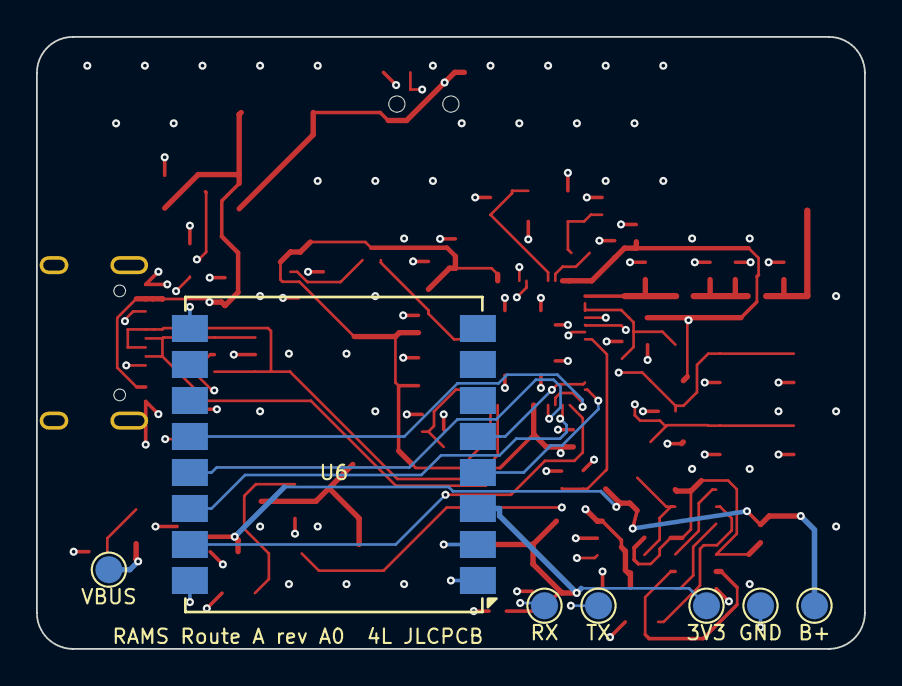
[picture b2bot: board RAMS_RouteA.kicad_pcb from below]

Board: 4 copper layers, 46.0 x 34.0 mm, 71 parts (7 on the bottom side), 43 nets.

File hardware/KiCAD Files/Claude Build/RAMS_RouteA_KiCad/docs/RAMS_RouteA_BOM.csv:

Refs,Qty,Value,Footprint,Source,Side,Notes
ANT1,1,2450AT18B100E,Johanson_2450AT18B100_3216,You own it,Top,Terminal 2 is NC. Keep ALL copper (all layers) out of the antenna keep-out. Tune with pi-network.
BZ1,1,Buzzer 9650 active 3V,Buzzer_SMD_9650,You own it,Top,Footprint from Rev A (2 pads 3.25 mm off-centre): MEASURE your buzzer.
C1 C2,2,4.7uF,C_0603_1608Metric,You own it,Top,VBUS bulk / charger input; charger BAT cap
C3 C7 C9 C10 C11 C12 C14 C25 C26,9,100nF,C_0402_1005Metric,You own it,Top,ADC filter; DW01A VCC filter; LED bypass (place at LED1 pin 4); LoRa HF decoupling; VDD3P3 decoupling; VDD3P3_CPU (pin 46); VDD3P3_RTC (pin 20); VDDA (pins 55/56); VDD_SPI (Espressif: add 0.1uF + 1uF)
C4 C5 C8 C16 C24,5,10uF,C_0603_1608Metric,You own it,Top,"3V3 bulk next to MCU (TX bursts); LDO input; LDO output; LoRa TX burst reservoir (placed on top, above the module); VDD3P3 bulk (Espressif: 10uF at VDD3P3)"
C6 C15 C17,3,1uF,C_0402_1005Metric,You own it,Top,EN RC delay; LDO output HF; VDD_SPI
C13,1,10nF,C_0402_1005Metric,You own it,Top,VDDA HF
C18 C19,2,12pF,C_0402_1005Metric,You own it,Top,crystal load cap
C20 C21,2,1.5pF,C_0402_1005Metric,BUY on Shopee,Top,"chip-end shunt (Espressif range 1.2-1.8pF, C0G 0402); shunt (Espressif range 1.2-1.8pF, C0G 0402)"
C22 C23,2,DNP,C_0402_1005Metric,Do not fit (tuning slot),Top,antenna pi shunt slot
D1,1,USBLC6-2SC6,SOT-23-6,You own it,Top,
D2,1,SS14,D_SMA,You own it,Top,"VBUS -> system, blocks back-feed"
D3,1,1N4148W,D_SOD-123,You own it,Top,buzzer clamp diode
FB1 L1 R16,3,0R,R_0402_1005Metric,You own it,Top,"VDD3P3 LC-filter slot: 0R now; try ferrite/inductor if RF noisy; antenna pi-network series slot; series on XTAL_P: Espressif suggests 24 nH (optional buy), 0R works first"
J1,1,USB-C 16P,USB_C_Receptacle_HRO_TYPE-C-31-M-12,You own it,Top,"Your 16P USB-C (Shopee clone). Footprint = HRO TYPE-C-31-M-12: MEASURE your part (pad pitch, shell legs) before ordering."
J2,1,Battery JST-SH 2P,JST_SH_SM02B-SRSS-TB_1x02-1MP_P1.00mm_Horizontal,You own it,Top,"Pin1 = +, Pin2 = -. CHECK your battery plug polarity before connecting!"
L2,1,2.0nH,L_0402_1005Metric,You own it,Top,series L (Espressif range 2.0-3.0 nH)
LED1,1,WS2812B-2020,LED_WS2812B-2020_PLCC4_2.0x2.0mm,You own it,Top,"Your 2020 LED (pin1 DOUT, 2 GND, 3 DIN, 4 VDD). Runs from +3V3. Worldsemi: V6 version is rated 3.3-5.3 V; older 2020 is rated 3.7-5.3 V - check your listing."
Q1,1,AO3401,SOT-23,You own it,Top,"P-FET power path: ON on battery, OFF when USB present"
Q2,1,BC817-25,SOT-23,You own it,Top,NPN low-side buzzer switch
Q3,1,FS8205A,SOT-23-6,You own it,Top,SOT-23-6 pinout is vendor-dependent: verify with a multimeter before soldering (see test list).
R1 R2,2,5.1k,R_0805_2012Metric,Your 0805 kit (verify value),Top,USB-C CC1 pulldown; USB-C CC2 pulldown
R3 R4 R17,3,33R,R_0402_1005Metric,You own it,Top,LED data series; USB D+ series; USB D- series
R5,1,4.3k,R_0402_1005Metric,You own it,Top,PROG: ~233 mA charge (if chip follows LTC4054 equation)
R6 R13,2,100k,R_0805_2012Metric,Your 0805 kit (verify value),Top,Q1 gate pulldown (gate is the VBUS net); base pulldown
R7,1,330R,R_0805_2012Metric,Your 0805 kit (verify value),Top,DW01A VCC filter
R8 R12,2,1k,R_0805_2012Metric,Your 0805 kit (verify value),Top,DW01A current-sense input -> system GND (not B_MINUS); base resistor
R9 R10,2,10k,R_0805_2012Metric,Your 0805 kit (verify value),Top,EN pull-up (Espressif RC: 10k + 1uF); GPIO0 pull-up (Espressif: recommended)
R14,1,330k,R_0402_1005Metric,You own it,Top,battery divider top
R15,1,180k,R_0402_1005Metric,You own it,Top,battery divider bottom (ratio 2.833)
SW1,1,MSK12C02,SW_SPDT_PCM12,You own it,Top,Slide switch drives AP2112K EN. Footprint = C&K PCM12 as in Rev A: verify against your MSK-12C02.
SW2,1,RESET,SW_Push_1P1T_NO_CK_KMR2,You own it,Top,Tact 3x4x2 2-pin SMD (your Order 8/23)
SW3,1,BOOT/CANCEL,SW_Push_1P1T_NO_CK_KMR2,You own it,Top,Hold at power-up = download mode; app may use as cancel button
TP1,1,3V3,TestPoint_Pad_D1.5mm,You own it,Top,
TP2,1,GND,TestPoint_Pad_D1.5mm,You own it,Top,
TP3,1,VBUS,TestPoint_Pad_D1.5mm,You own it,Top,
TP4,1,B+,TestPoint_Pad_D1.5mm,You own it,Top,
TP5,1,TX,TestPoint_Pad_D1.5mm,You own it,Top,UART0 TX (GPIO43) bring-up pad
TP6,1,RX,TestPoint_Pad_D1.5mm,You own it,Top,UART0 RX (GPIO44) bring-up pad
U1,1,ESP32-S3FH4R2,QFN-56-1EP_7x7mm_P0.4mm_EP4x4mm,You own it,Top,EP footprint = KiCad stock 4x4 (as in the KiCad symbol). Confirm vs Espressif FH4R2 drawing.
U3,1,LTC4054ES5-4.2 (LTH7R),SOT-23-5,You own it,Top,Li-ion charger. CHRG left open (no indicator).
U4,1,DW01A,SOT-23-6,You own it,Top,
U5,1,AP2112K-3.3,SOT-23-5,You own it,Top,
U6,1,Ra-02 SX1278,Ai-Thinker-Ra-01-LoRa,You own it,Bottom,"Bottom side, hand soldered. Ra-02 has an ONBOARD spring antenna (no U.FL / external antenna)."
Y1,1,40MHz 3225,Crystal_SMD_3225-4Pin_3.2x2.5mm,You own it,Top,Espressif needs +/-10 ppm; unknown for your Shopee crystal. Check CL and tune C9/C10 if Wi-Fi/BLE flaky.
